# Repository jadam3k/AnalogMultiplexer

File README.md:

# Analog Multiplexer Project
## They told me not to add screenshots from the basket
This is a simple **analog multiplexer** I put together.  
It allows me to connect multiple analog components, like sensors, to a single input on a microcontroller.  

I built this project mainly as a **learning exercise** to get more comfortable with how multiplexers work in real-life circuits.

---

## Bill of Materials (BOM)

Here is the list of components used in this project.  
Where possible, I have added links to datasheets for reference.

| ID | Component Name             | Description                                 | Quantity | 
| -- | -------------------------- | ------------------------------------------- | -------- | 
| 1  | 2-pin 2.54mm Female Header | Single row, 2.54 mm pitch female PCB header | 1        | 
| 2  | 8-pin 2.54mm Female Header | Single row, 2.54 mm pitch female PCB header | 1        | 
| 3  | 4-pin 2.54mm Female Header | Single row, 2.54 mm pitch female PCB header | 1        |
| 4  | CD74HC4052E                | 2-channel 4:1 analog multiplexer IC         | 1        | 
| 5  | DW127R-22-06-34            | 6-pin wire-to-board connector               | 1        | 

---

## Project Images

Below are some pictures of the multiplexer in action:

**1. Full View of the PCB**  

**2. Close-up of the Headers**  

**3. Multiplexer Wiring**  

---

## How it Works

1. The **CD74HC4052E** acts as a 2-channel analog multiplexer.  
2. The microcontroller selects which sensor to read vi

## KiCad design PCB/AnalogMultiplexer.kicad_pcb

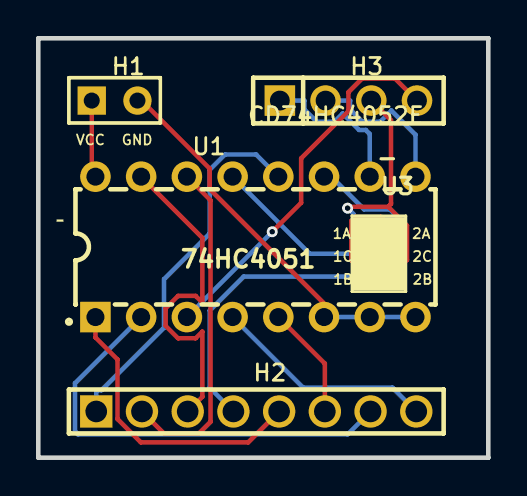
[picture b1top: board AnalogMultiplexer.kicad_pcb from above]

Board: 2 copper layers, 25.0 x 23.3 mm, 5 parts (0 on the bottom side), 16 nets.

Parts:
H1: HDR-F-2.54_1x2; HDR-F-2.54_1X2
H2: Header-Female-2.54_1x8; HDR-TH_8P-P2.54-V-F-1
H3: 2.54-1*4P母; HDR-TH_4P-P2.54-V-F
U1: CD74HC4052E; PDIP-16_L19.7-W6.6-P2.54-LS7.8-BL
U3: _

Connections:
A1Y0: H2.1, U1.12
A1Y1: H2.2, U1.14
A1Y2: H2.3, U1.15
A1Y3: H2.4, U3.2, U3.5
A2Y0: H2.5, U1.1
A2Y1: H2.6, U1.5
A2Y2: H2.7, U1.2
A2Y3: H2.8, U1.4
GND: H1.2, U1.6, U1.7, U1.8
IO_0: H3.1, U1.10
IO_1: H3.2, U1.9
IO_2: H3.3, U3.1, U3.6
IO_3: H3.4, U1.3
SW1C: U1.13, U3.3
SW2C: U1.11, U3.4
VCC: H1.1, U1.16

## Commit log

2025-11-21 Refactor README to simplify project description
    Removed markdown header and emphasized project description.
2025-11-21 Revise README for analog multiplexer project
    Updated project description for clarity and emphasis on learning.
2025-11-21 Add screenshots to README
    Added screenshots to README for better visualization.
2025-11-21 Fix formatting of screenshots section in README
2025-11-21 Add bill of materials (bom.csv) with components
2025-11-21 Add quotes to component descriptions in bom.csv
    Updated descriptions in bom.csv to use quotes.
2025-11-21 Update README with project details and BOM
    Expanded project details and added Bill of Materials.
2025-11-21 Add placeholder for screenshots in README
    Added a placeholder for a screenshot section.
